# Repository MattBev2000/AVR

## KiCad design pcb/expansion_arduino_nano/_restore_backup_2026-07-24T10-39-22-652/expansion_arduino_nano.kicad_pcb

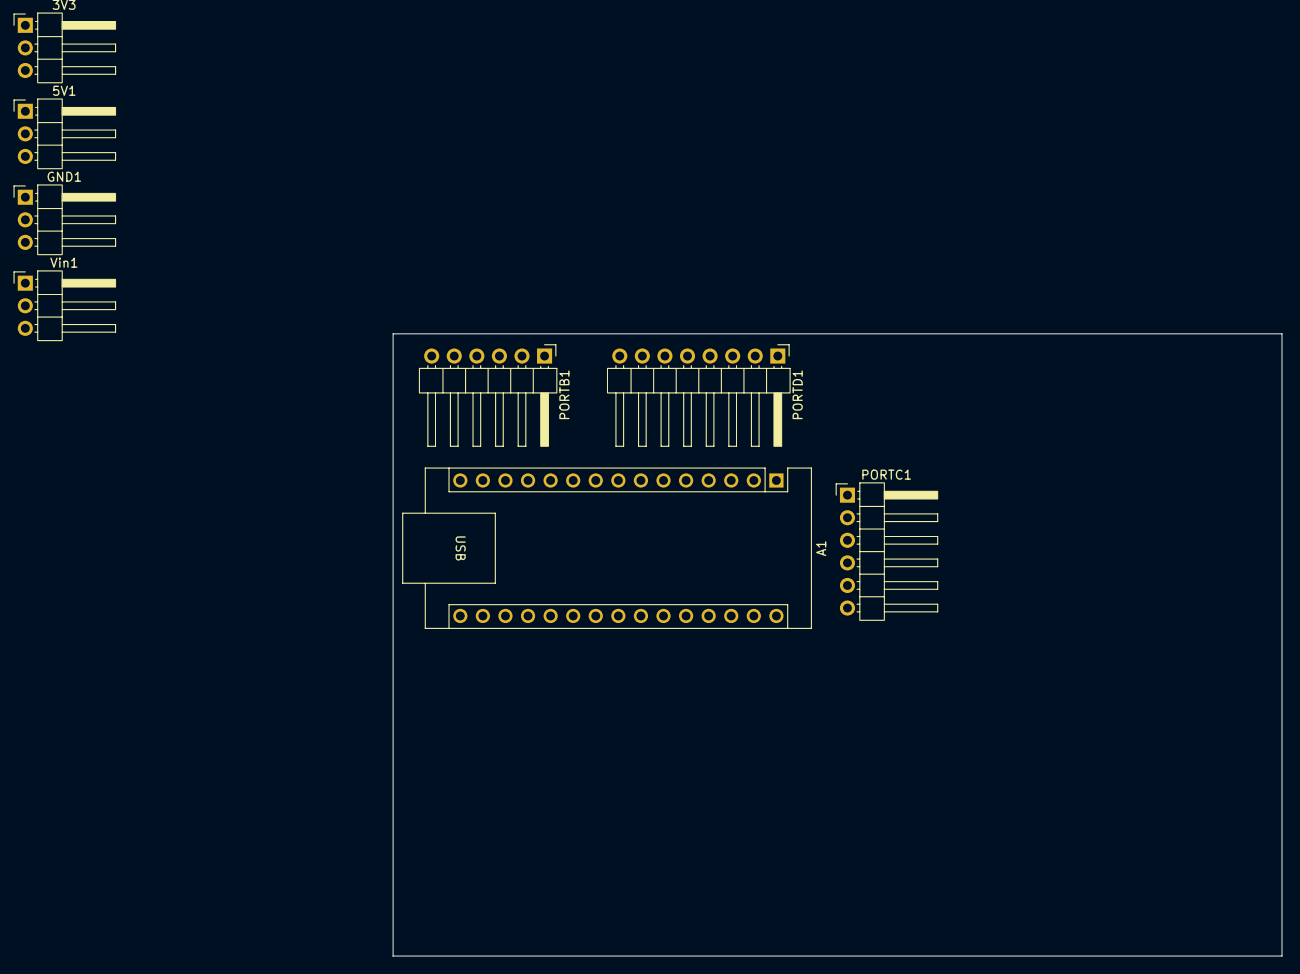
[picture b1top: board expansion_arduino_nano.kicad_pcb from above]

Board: 2 copper layers, 100.0 x 70.0 mm, 8 parts (0 on the bottom side), 24 nets, no tracks yet.

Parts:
3V3, 5V1: PinHeader_1x03_P2.54mm_Horizontal
A1: Arduino_Nano_v3.x; Arduino_Nano
GND1: PinHeader_1x03_P2.54mm_Horizontal
PORTB1: PinHeader_1x06_P2.54mm_Horizontal
PORTC1: PinHeader_1x06_P2.54mm_Horizontal
PORTD1: PinHeader_1x08_P2.54mm_Horizontal
Vin1: PinHeader_1x03_P2.54mm_Horizontal

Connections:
/3V3: 3V3.1, 3V3.2, 3V3.3, A1.27 (+5V)
/5V: 5V1.1, 5V1.2, 5V1.3, A1.17 (3V3)
/PB0: A1.11 (D8), PORTB1.1
/PB1: A1.12 (D9), PORTB1.2
/PB2: A1.13 (D10), PORTB1.3
/PB3: A1.14 (D11), PORTB1.4
/PB4: A1.15 (D12), PORTB1.5
/PB5: A1.16 (D13), PORTB1.6
/PC0: A1.19 (A0), PORTC1.1
/PC1: A1.20 (A1), PORTC1.2
/PC2: A1.21 (A2), PORTC1.3
/PC3: A1.22 (A3), PORTC1.4
/PC4: A1.23 (A4), PORTC1.5
/PC5: A1.24 (A5), PORTC1.6
/PD0: A1.2 (D0/RX), PORTD1.1
/PD1: A1.1 (D1/TX), PORTD1.2
/PD2: A1.5 (D2), PORTD1.3
/PD3: A1.6 (D3), PORTD1.4
/PD4: A1.7 (D4), PORTD1.5
/PD5: A1.8 (D5), PORTD1.6
/PD6: A1.9 (D6), PORTD1.7
/PD7: A1.10 (D7), PORTD1.8
/VIN: A1.30 (VIN), Vin1.1, Vin1.2, Vin1.3
GND: A1.4 (GND), A1.29 (GND), GND1.1, GND1.2, GND1.3
